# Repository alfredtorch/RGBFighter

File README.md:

🚥 Micro ESP-01 board for addressable pixel control 🚥 ... suits to every place and mostly to any needs!
Only a power bank and a smartphone are needed and you're good to go with your mobile setup.

* Small : +- 14x32mm & Lightweight : +- 4gr
* ESP8266 based (Support for Arduino)
* Designed for common LED Strips like WS2812 with level shifting
* Connection over 2,54 mm 3 Pin for direct soldering, JST or screw terminal (Version Strip or Panel)
* Power and Progamming over USB (CP2104 nodeMCU design)
* User Input for One Button OR IR Receiver
* [WLED](https://github.com/Aircoookie/WLED "WLED's Github page") compatible
* Inspirations from Adafruit, Sparkfun and many others

# ⚡️PCB 

# 🔦 Hardware

At the moment I have no possibility for a larger production and distribution. Of course, I am ready for any cooperation to industrialize the production. Happy to get any proposition.

## 🗺 Design Files

Designed in Eagle, in a messy way! Sorry! The related files are available under /Hardware.
Name | Description 
--- | ---
ButtonPanel | Panel and Button
ButtonStrip | Strip and Button
IR | Strip and IR Receiver
PowerRail | Power for 8 Strips
PowerDistributorX30 | 5 Ports XT-30 Connector

## 🛠 For DIY'er:
All you need are steady hands for the soldering part, specially the QFN. A reflow or hot plate is suggested.
The thickness of the board should be 1,2mm in order to sold the vertical USB firmly. The parts can be easily ordered from the common suppliers.

## 💰BOM

Part Name | Quantity | Price | Supply Link | Notes 
--- | --- | --- | --- | ---
Board RGBFighter | 1 | 0,02€ | [DirtyCheapPCB](https://dirtypcbs.com/store/pcbs/buy/108056/rgborder10x10january2019-zip) | Panelised Design files of Panel-Strip-USB Versions
ESP-01 MCU | 1x | 2€ | [Amazon](https://amzn.to/3qxXip7) | The brain with Wifi!
CP2104 USB Controller | 1x | 3€ | Mouser, ... | need for progamming : alternative [ESP-01 Flasher Amazon](https://amzn.to/3A2HptF) - [Aliexpress](https://s.click.aliexpress.com/e/_9JcISN)
Micro USB Vertical | 1x | 0,5€ | [Aliexpress](https://s.click.aliexpress.com/e/_AaeVzr)
Resistor Array 603 10k | 2x | 0,2€ | Mouser, ... | Pull-up registors for programming and normal operation
Transistor MMBT2222 | 2x | 0,2€ | Mouser, ... | need for programming, NPN Type
Capacitor 0805 | 3x | 0,2€ | Mouser, ... | Various values : schematics
Inducator 2.2uH | 1x | 0,2€ | Mouser, ... | NRH2412T2R2MNGH
3V3 Step Down Converter | 1x | 1,2€ | Mouser, ... | LM3671
Reistor 300Ohm 0805 | 1x | 0,2€ | Mouser, ... | basic pin protection 
Level Shifter SN74LVC1T45DBV  | 1x | 0,2€ | Mouser, ... | for the right Voltage on the Data bus
Button G71Y | 2x | 0,2€ | [Aliexpress](https://s.click.aliexpress.com/e/_A68Ds9) | MCU & Reset User Input
IR Receiver | 1x | 0,2€ | [Aliexpress](https://s.click.aliexpress.com/e/_A7jhiZ) |IR Control Version

🙏 Please if you need to shop for parts, it would be great that you use the supply links below. As they are affilated, you're supporting me directly to continue to deliver new projects to the community! Thank you ❤️

# 🎆 Versions

# 📖 History and Evaluation

It started longtime ago when I wanted an easy way to drive my pixels. First pcb version was sended to fabrication in july 2016. 
Since the project evolved into something more advanced and more mature!

## 🔍 Development Phase
ToDo | Remarks
--- | --- 
Easy Boards | Design boards without programming chip but with easy to solder buttons and voltage converter 
Documentation | Improve the transfer of knowledge
Big production | Looking forward to have some input, help to release it massivly, if wanted.

# 🛒 Accessories

Most of these parts can be laser cutted. The related files are available under Hardware/RGBFighterLaserParts.dxf

# 👶🏼 First Steps & Ideas

⚠️Don't mess with the power - no polarity or whatever protection ⚠️

⚠️Vertical USB is fragile - Handle with care ⚠️

## 🤏🏽 Pinout
Pin | Function
--- | ---
GPIO0 | Button Or InfraRed
GPIO2 | RGB Output | Recomanded Output from WLED

## 💾 Programming
You can directly check the [How-To from WLED](https://kno.wled.ge/basics/install-binary/)

## 🪛 Tutorials
see [Tutorials Page](https://github.com/alfredtorch/RGBFighter/blob/master/Tutorials.md)

Servo, Electro-Dipped, ...

---

# ⚖️ Licence
The MIT License (MIT)

Copyright (c) 2021 Max Schmit

Permission is hereby granted, free of charge, to any person obtaining a copy of this Hardware and associated documentation files (the "Hardware"), to deal in the Hardware without restriction, including without limitation the rights to use, copy, modify, merge, publish, distribute, sublicense, and/or sell copies of the Hardware, and to permit persons to whom the Hardware is furnished to do so, subject to the following conditions:

The above copyright notice and this permission notice shall be included in all copies or substantial portions of the Software.

THE HARDWARE IS PROVIDED "AS IS", WITHOUT WARRANTY OF ANY KIND, EXPRESS OR IMPLIED, INCLUDING BUT NOT LIMITED TO THE WARRANTIES OF MERCHANTABILITY, FITNESS FOR A PARTICULAR PURPOSE AND NONINFRINGEMENT. IN NO EVENT SHALL THE AUTHORS OR COPYRIGHT HOLDERS BE LIABLE FOR ANY CLAIM, DAMAGES OR OTHER LIABILITY, WHETHER IN AN ACTION OF CONTRACT, TORT OR OTHERWISE, ARISING FROM, OUT OF OR IN CONNECTION WITH THE SOFTWARE OR THE USE OR OTHER DEALINGS IN THE SOFTWARE.

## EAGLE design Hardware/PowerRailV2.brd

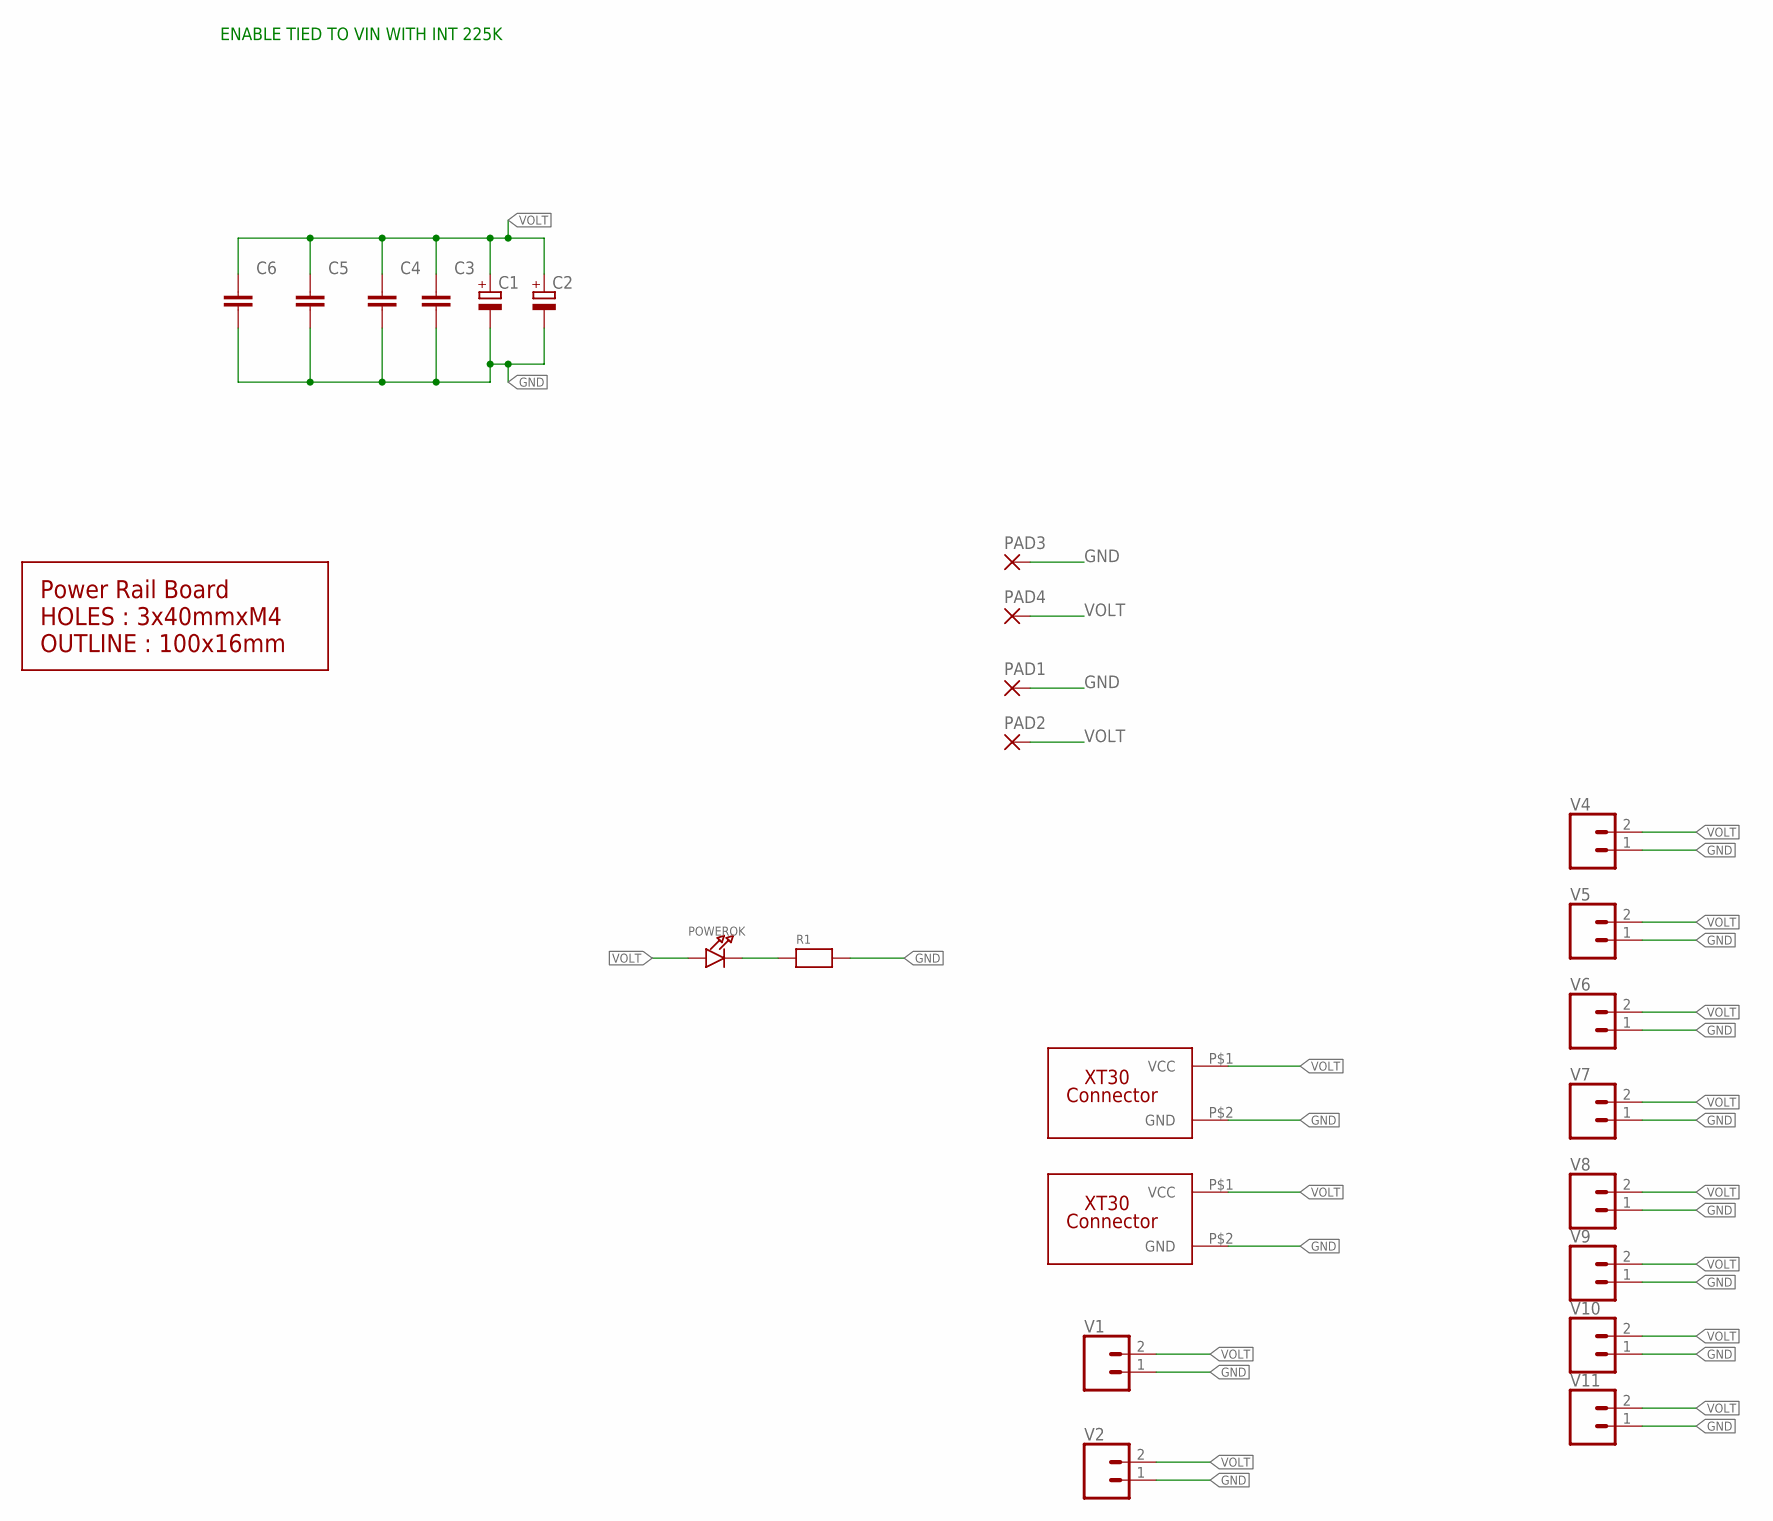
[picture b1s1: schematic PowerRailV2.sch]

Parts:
C1, C2: CPOL-EUE5-6; E5-6
C3, C4: CAPACITOR_NPOL-0805; C805
C5, C6: CAPACITOR_NPOL-1206; C1206
PAD1, PAD2, PAD3, PAD4: SMD2; SMD1,27-2,54
POWEROK: LED0805; CHIPLED_0805
R1: RESISTOR0805; 0805
U$3: BOARD_POWERRAI_PCB; POWERRAIL_8-LED
U$4, U$6: XT30; XT30-VERT
V1, V2, V4, V5, V6, V7, V8, V9, V10, V11: CONN_023.5MM; SCREWTERMINAL-3.5MM-2

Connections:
GND: C1.-, C2.-, C3.2, C4.2, C5.2, C6.2, PAD1.1, PAD3.1, R1.2, U$4.P$2 (GND), U$6.P$2 (GND), V1.1, V2.1, V4.1, V5.1, V6.1, V7.1, V8.1, V9.1, V10.1, V11.1
unnamed: POWEROK.C, R1.1
VOLT: C1.+, C2.+, C3.1, C4.1, C5.1, C6.1, PAD2.1, PAD4.1, POWEROK.A, U$4.P$1 (VCC), U$6.P$1 (VCC), V1.2, V2.2, V4.2, V5.2, V6.2, V7.2, V8.2, V9.2, V10.2, V11.2

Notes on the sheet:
ENABLE TIED TO VIN WITH INT 225K

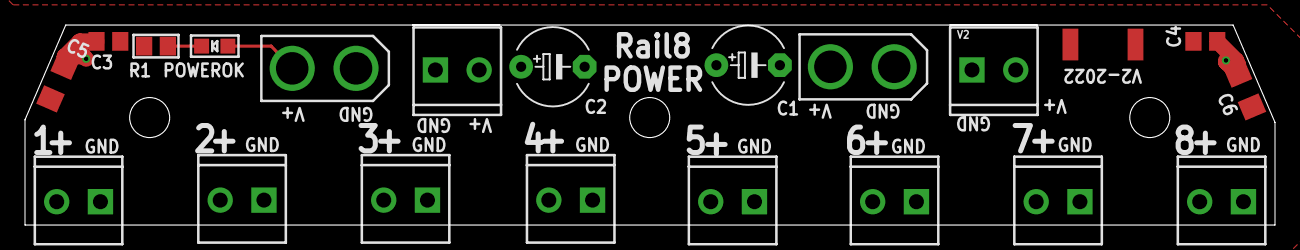
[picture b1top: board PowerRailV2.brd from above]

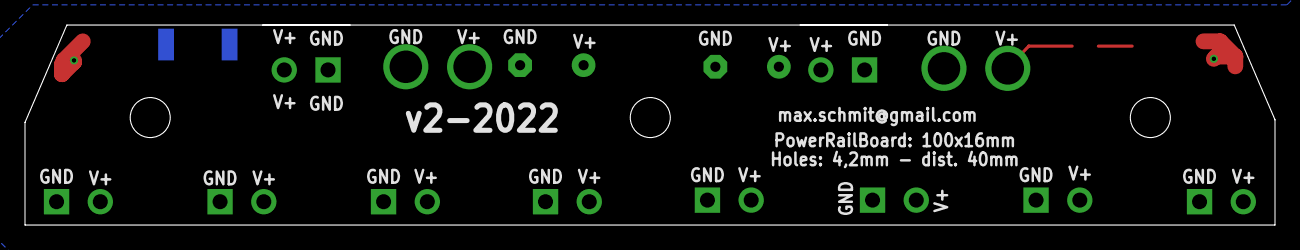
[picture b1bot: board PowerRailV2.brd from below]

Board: 2 copper layers, 100.0 x 16.0 mm, 25 parts (2 on the bottom side), 3 nets.

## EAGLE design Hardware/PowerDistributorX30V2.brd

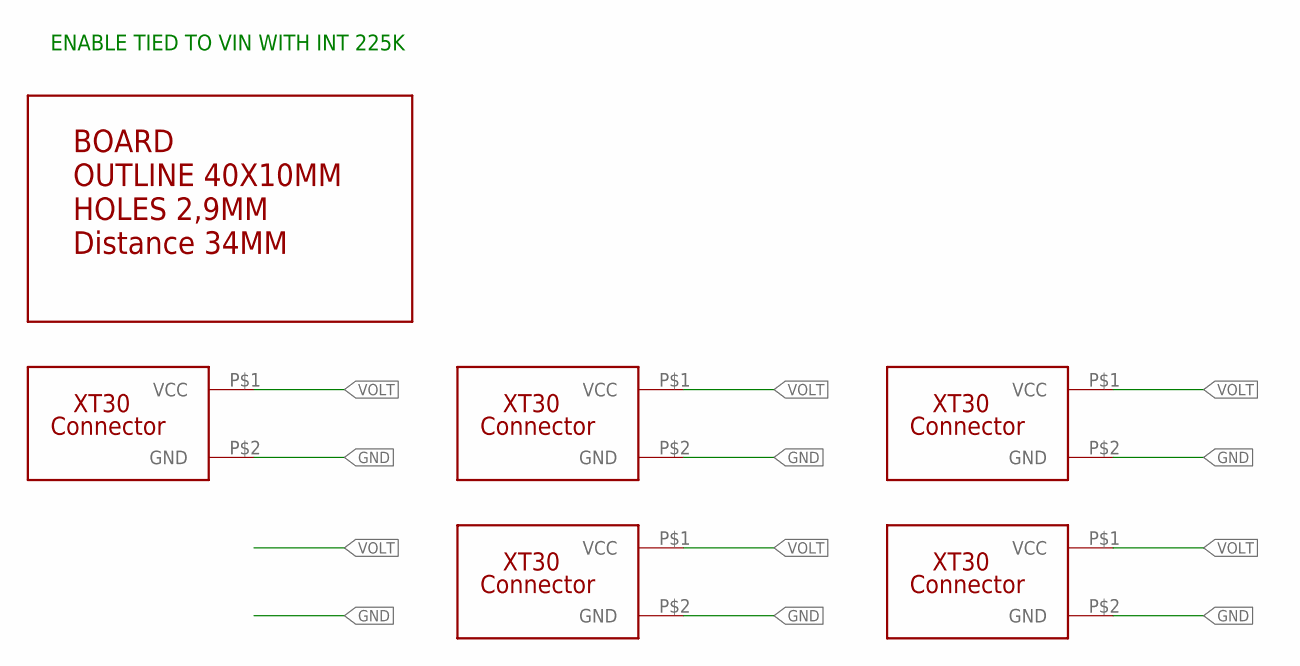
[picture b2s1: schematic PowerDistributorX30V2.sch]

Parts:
U$1: BOARD40X10; BOARD_40X10-34HOLES
U$2, U$4, U$5, U$6, U$7: XT30; XT30-VERT

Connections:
GND: U$2.P$2 (GND), U$4.P$2 (GND), U$5.P$2 (GND), U$6.P$2 (GND), U$7.P$2 (GND)
VOLT: U$2.P$1 (VCC), U$4.P$1 (VCC), U$5.P$1 (VCC), U$6.P$1 (VCC), U$7.P$1 (VCC)

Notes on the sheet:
ENABLE TIED TO VIN WITH INT 225K

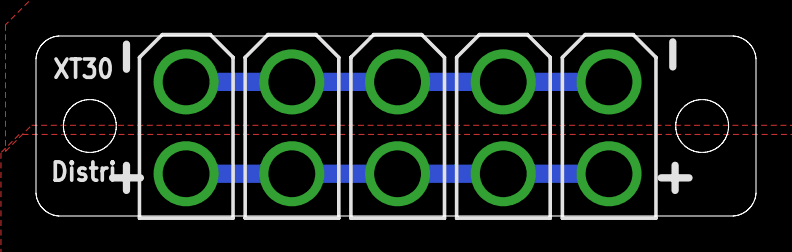
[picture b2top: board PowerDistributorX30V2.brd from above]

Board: 2 copper layers, 40.0 x 10.0 mm, 6 parts (0 on the bottom side), 2 nets.

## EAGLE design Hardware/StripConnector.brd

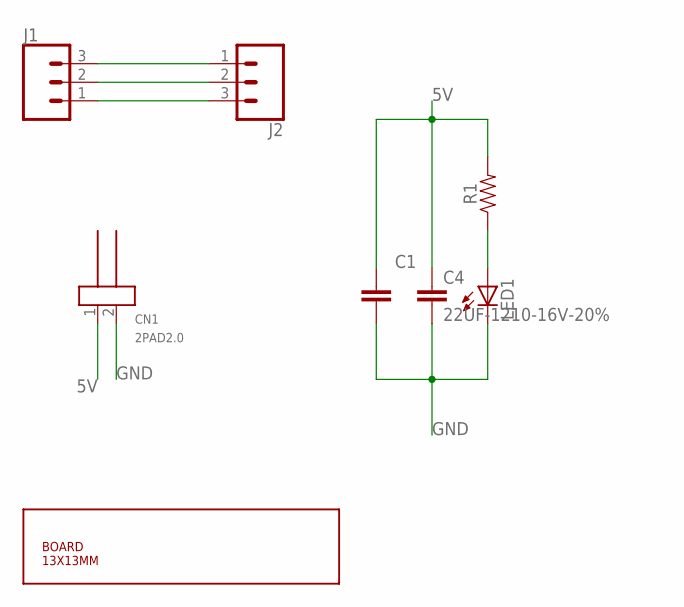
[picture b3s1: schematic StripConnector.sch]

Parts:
C1: CAPACITOR_NPOL-0805; C805
C4: 22UF-1210-16V-20%; 1210
CN1: 2PAD2.0; 2POLE_P2.0
J1, J2: CONN_03LONGPADS; 1X03_LONGPADS
LED1: LED-0805; LED-805
R1: 0805
U$1: BOARD_13X13MM; 13X13

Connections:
5V: C1.1, C4.1, CN1.1, J1.1, J2.3, R1.2
DATA: J1.2, J2.2
GND: C1.2, C4.2, CN1.2, J1.3, J2.1, LED1.C
unnamed: LED1.A, R1.1

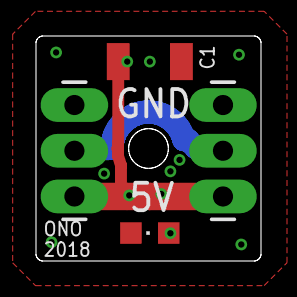
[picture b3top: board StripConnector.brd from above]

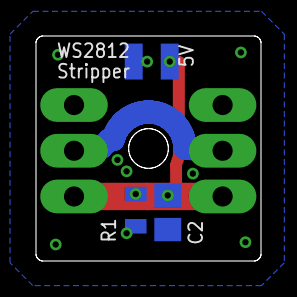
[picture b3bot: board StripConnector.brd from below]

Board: 2 copper layers, 12.5 x 12.5 mm, 8 parts (3 on the bottom side), 4 nets.

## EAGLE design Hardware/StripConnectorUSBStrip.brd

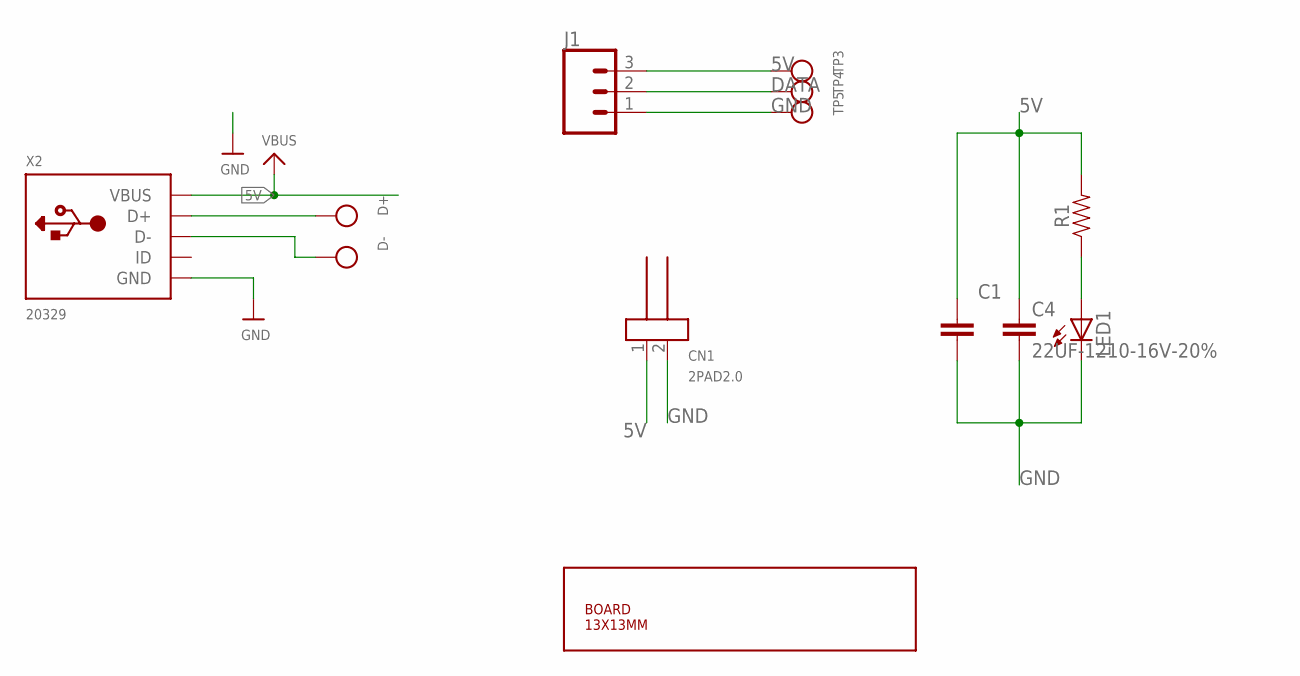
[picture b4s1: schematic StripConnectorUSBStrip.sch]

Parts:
C1: CAPACITOR_NPOL-0805; C805
C4: 22UF-1210-16V-20%; 1210
CN1: 2PAD2.0; 2POLE_P2.0
D+: TESTPOINTROUND1MM; TESTPOINT_ROUND_1MM
D-: TESTPOINTROUND1MM; TESTPOINT_ROUND_1MM
J1: CONN_03LONGPADS; 1X03_LONGPADS
LED1: LED-0805; LED-805
R1: 0805
TP3, TP4, TP5: TESTPOINTROUND1MM; TESTPOINT_ROUND_1MM
U$1: BOARD_13X13MM; 13X13
X2: 20329; 4UCONN_20329_V2

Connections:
5V: C1.1, C4.1, CN1.1, J1.3, R1.2, TP3.P$1, X2.VBUS
DATA: J1.2, TP4.P$1
GND: C1.2, C4.2, CN1.2, J1.1, LED1.C, TP5.P$1, X2.BASE@1 (GND), X2.BASE@2 (GND), X2.GND, X2.SPRT@1 (GND), X2.SPRT@2 (GND), X2.SPRT@3 (GND), X2.SPRT@4 (GND)
unnamed: D-.P$1, X2.D-
unnamed: LED1.A, R1.1
unnamed: D+.P$1, X2.D+

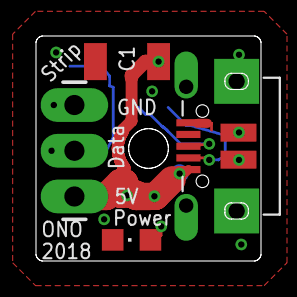
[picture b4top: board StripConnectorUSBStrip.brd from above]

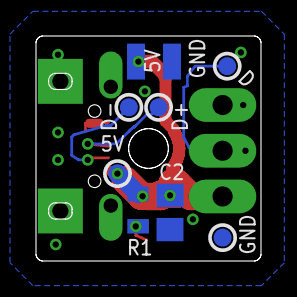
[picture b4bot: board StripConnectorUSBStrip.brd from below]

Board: 2 copper layers, 12.5 x 12.5 mm, 13 parts (8 on the bottom side), 6 nets.

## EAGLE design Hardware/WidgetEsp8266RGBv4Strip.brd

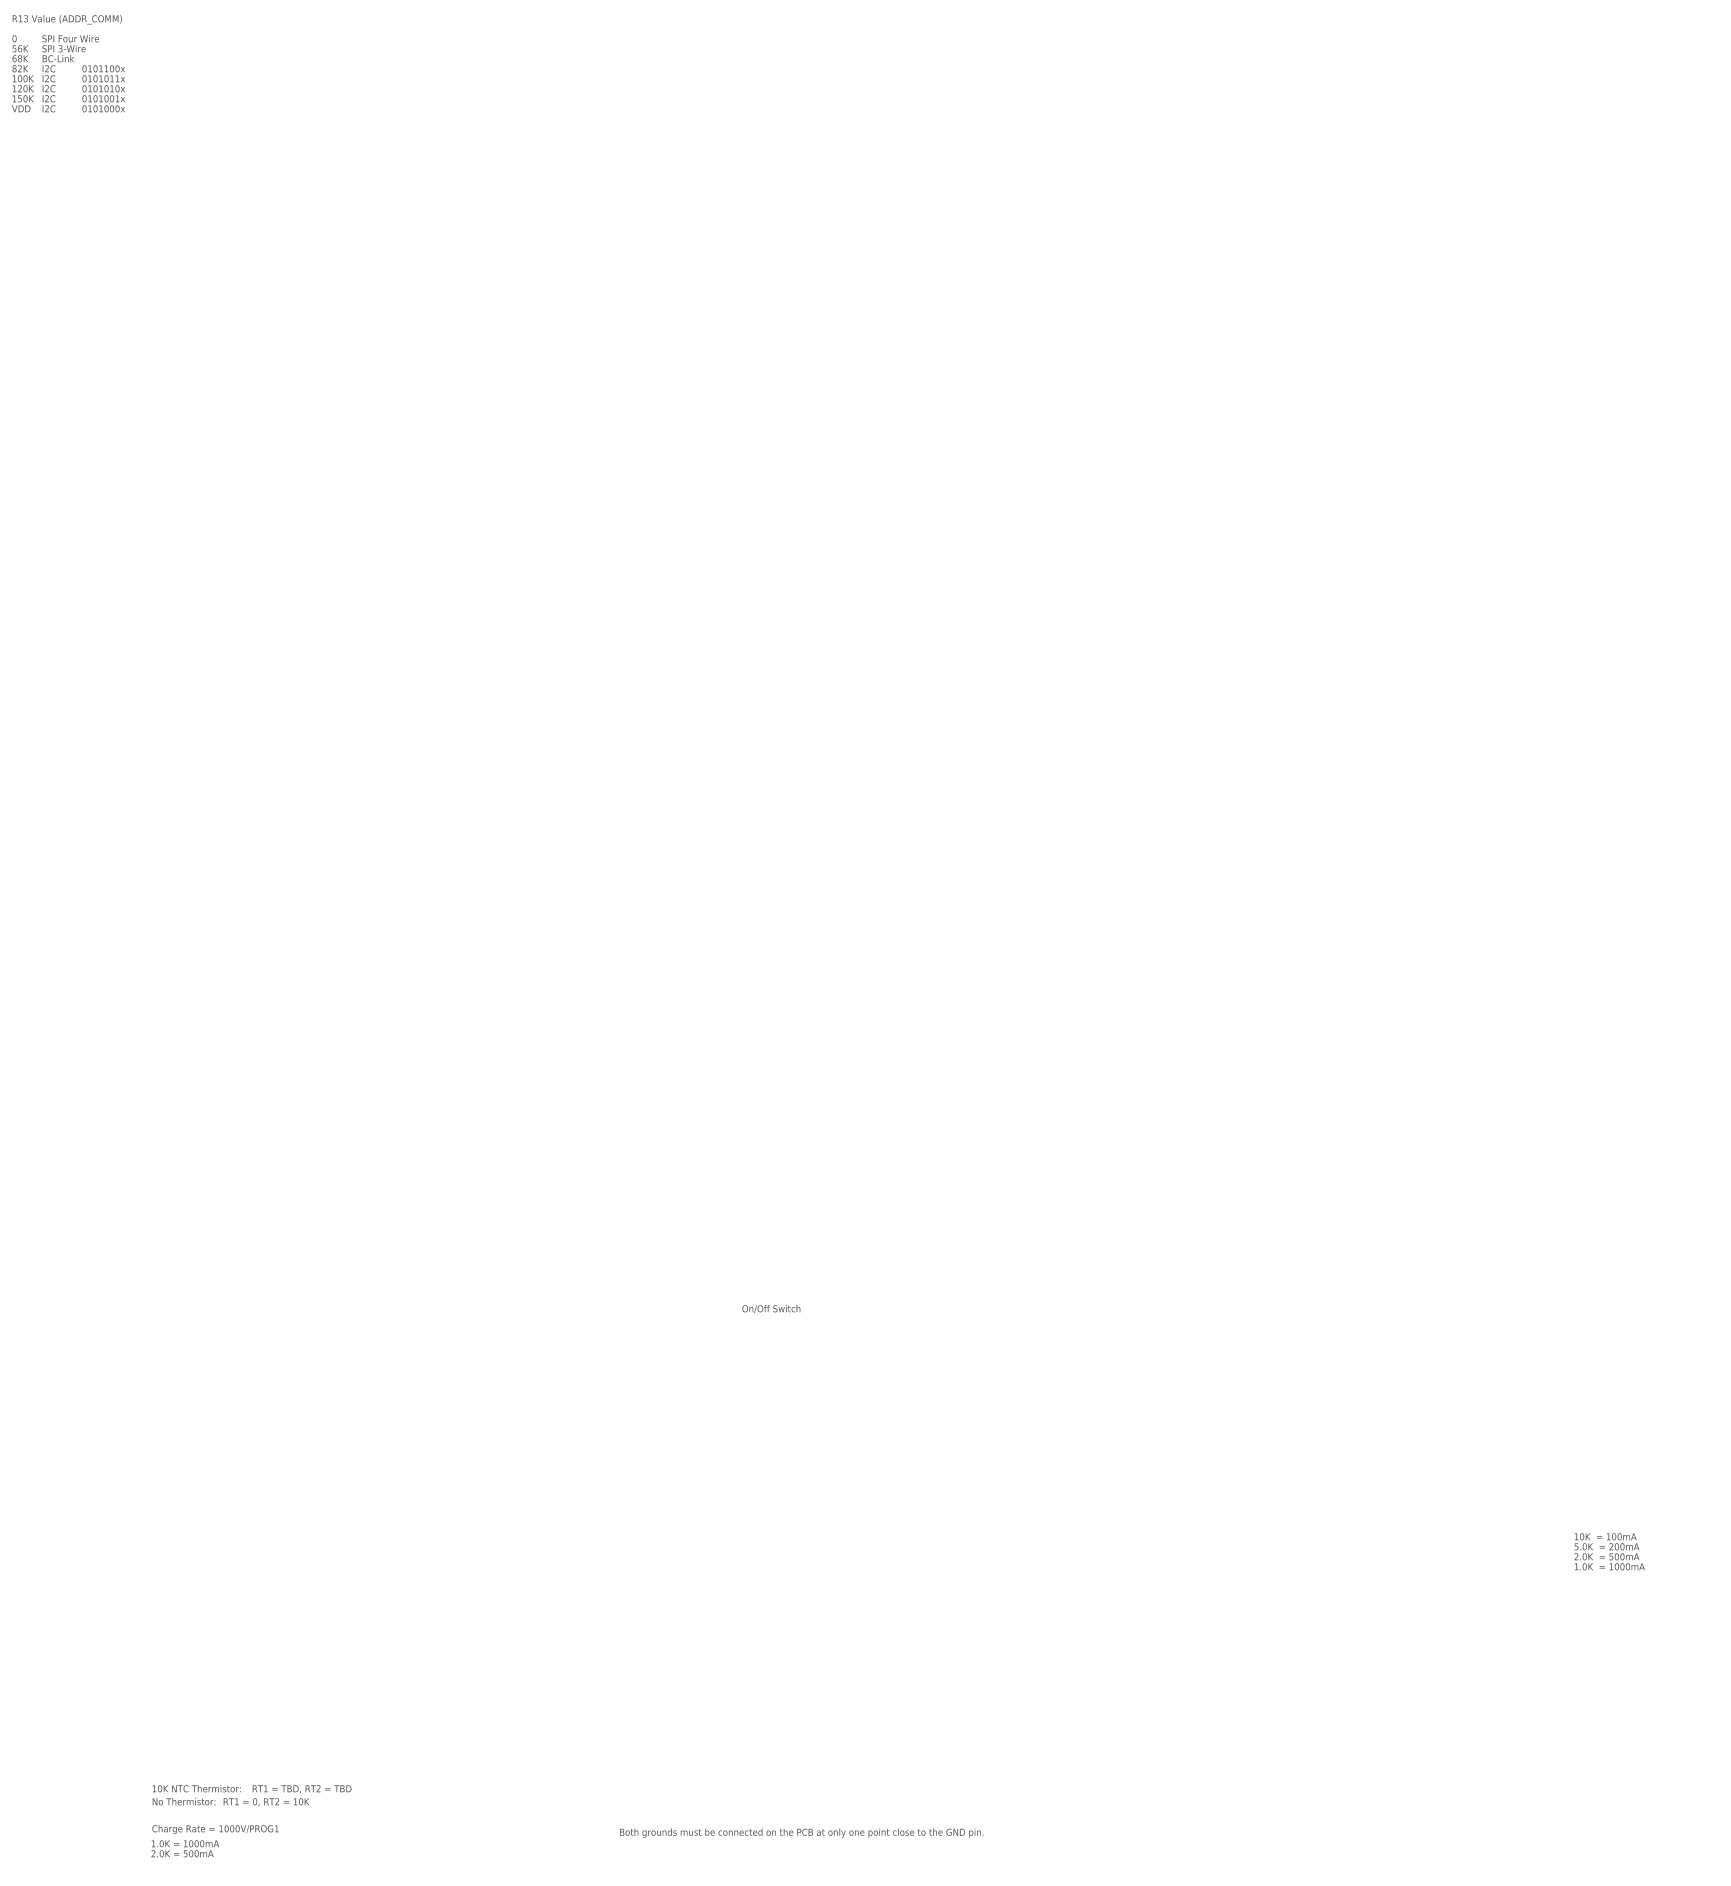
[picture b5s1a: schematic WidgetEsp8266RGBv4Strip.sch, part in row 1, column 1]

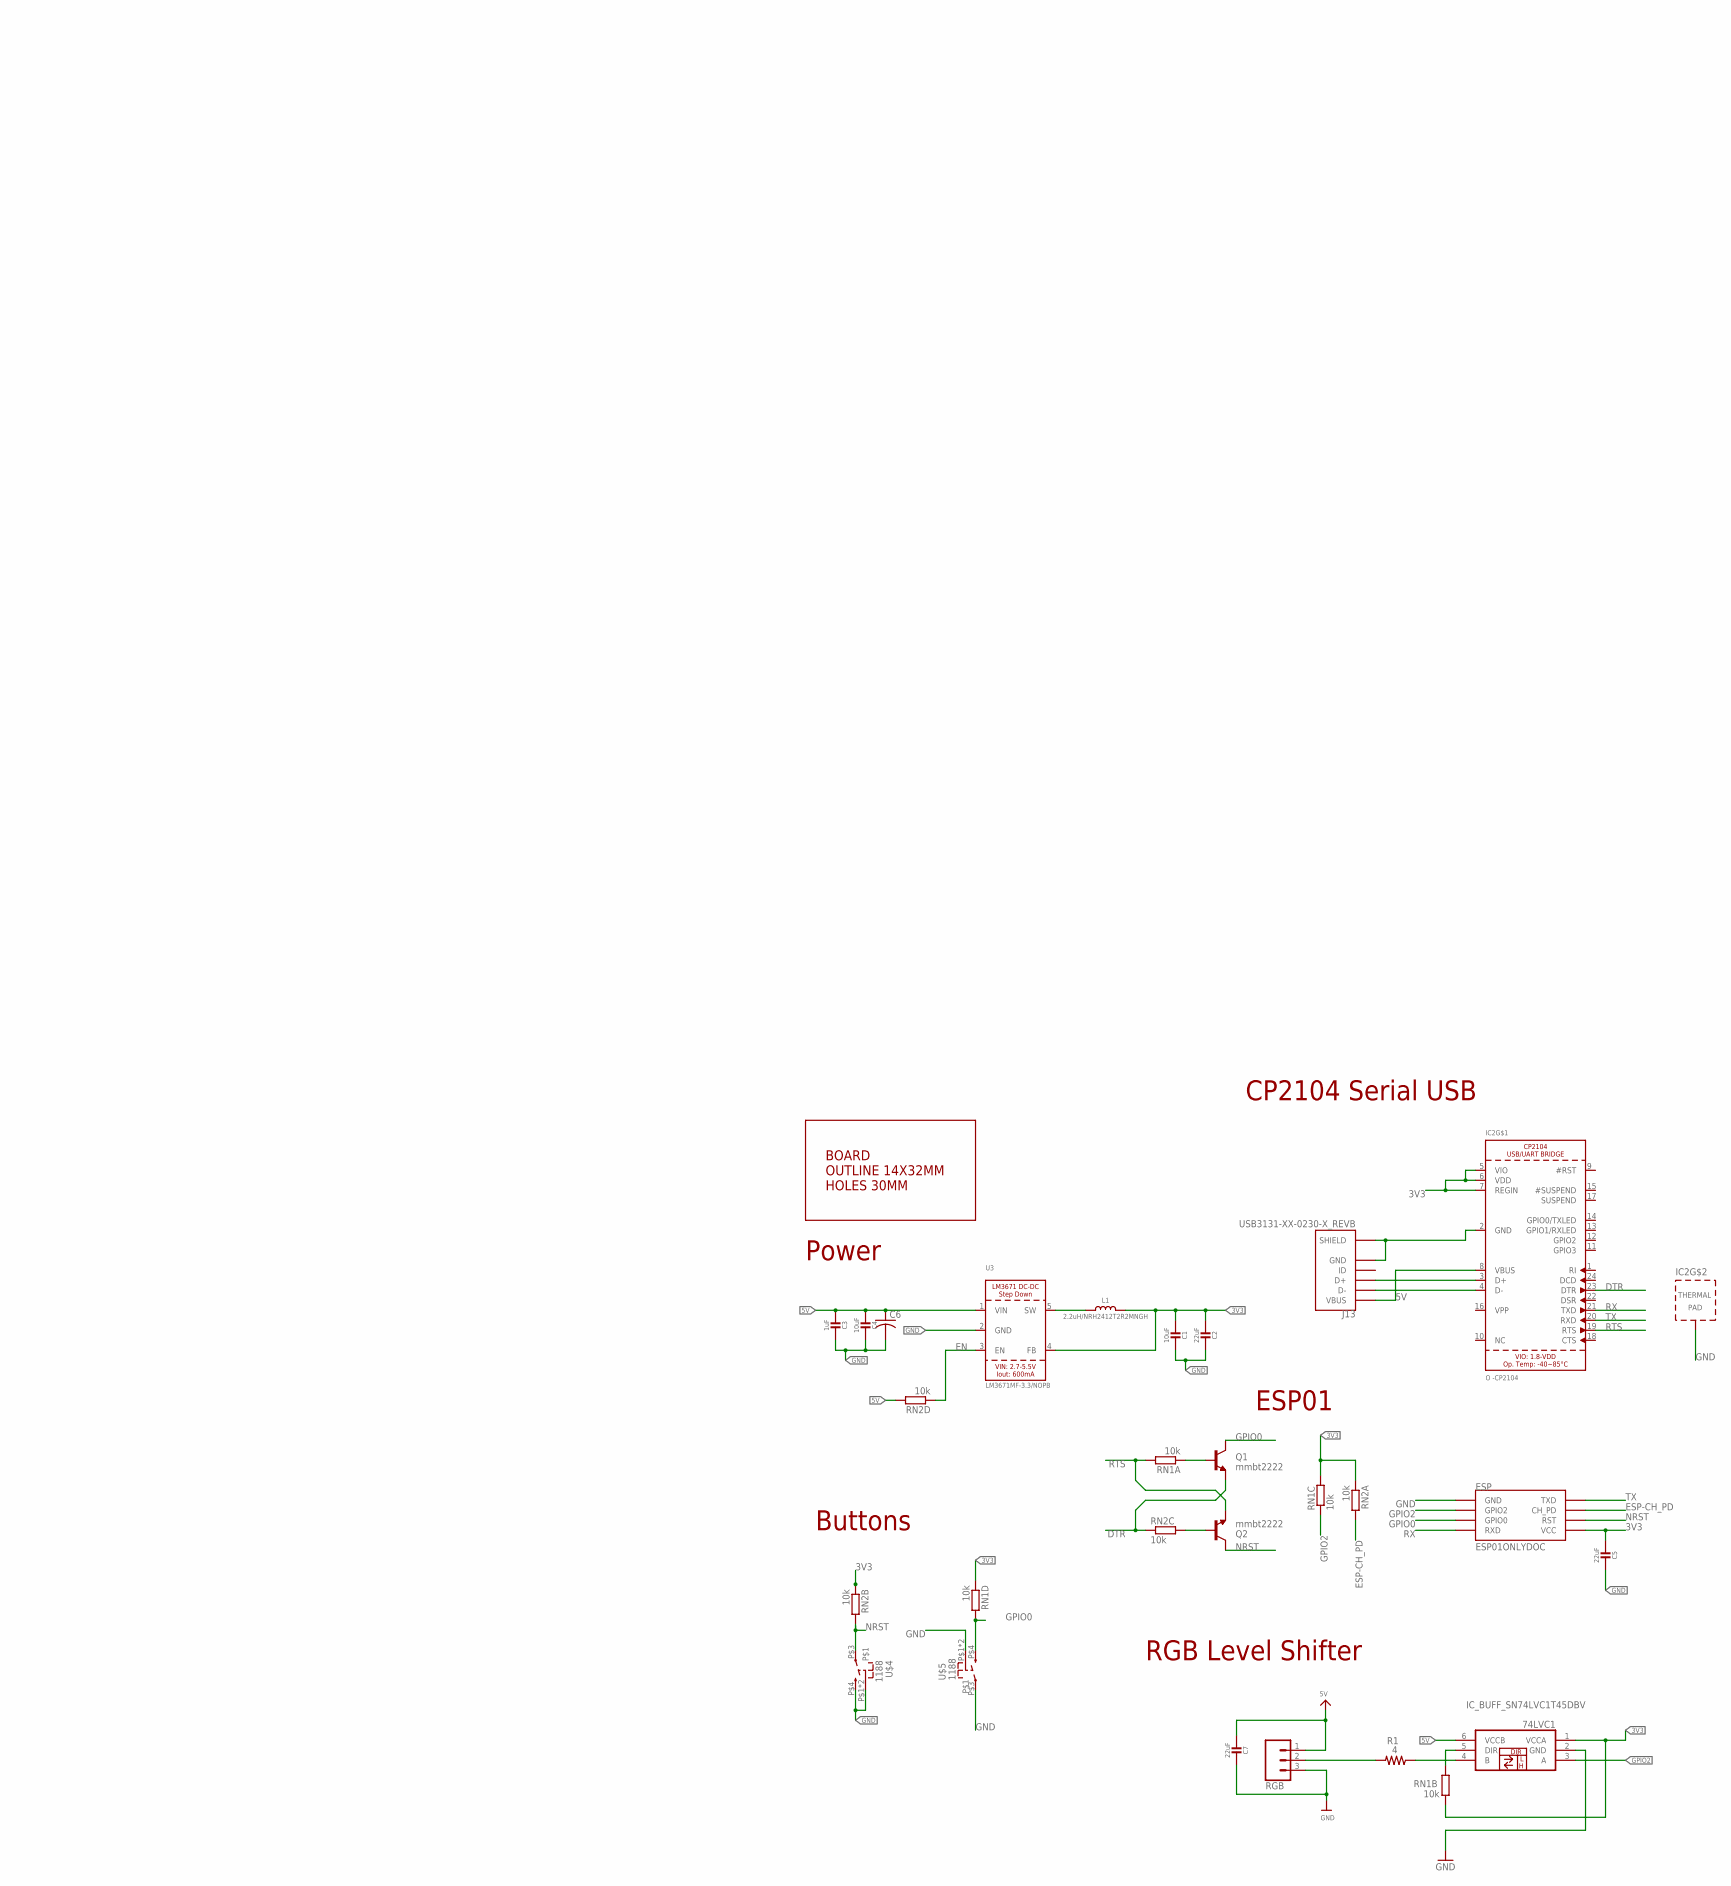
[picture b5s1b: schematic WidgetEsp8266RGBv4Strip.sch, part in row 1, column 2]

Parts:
74LVC1: IC_BUFF_SN74LVC1T45DBV; DBV-R-PDSO-G6
C1, C4: 10uF; 0805-NO
C2, C5, C7: 22uF; 0805-NO
C3: 1uF; 0805-NO
C6: C-USC3225; C3225
ESP: ESP01ONLYDOC; ESP01-NONOSILK
IC2: O -CP2104; QFN24_4MM_SMSC
J13: USB3131-XX-0230-X_REVB; GCT_USB3131-XX-0230-X_REVB
L1: 2.2uH/NRH2412T2R2MNGH; INDUCTOR_TAIYOYUDEN_NRH2412T
Q1, Q2: mmbt2222; SOT23-3
R1: 4; 0805
RGB: CONN_03LONGPADS; 1X03_LONGPADS
RN1, RN2: 10k; RN8P-4R-CRA06S
U3: LM3671MF-3.3/NOPB; SOT23-5
U$4, U$5: 1188
U$7: BOARD14X32; 14X32

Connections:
3V3: 74LVC1.1 (VCCA), C1.2, C2.2, C5.2, ESP.VCC, IC2.5 (VIO), IC2.6 (VDD), IC2.7 (REGIN), L1.2, RN1.4 (1), RN1.6 (2), RN1.7 (2), RN2.1, RN2.2 (1), U3.4 (FB)
5V: 74LVC1.6 (VCCB), C3.2, C4.2, C6.1, C7.2, IC2.8 (VBUS), J13.1 (VBUS), RGB.1, RN2.5 (2), U3.1 (VIN)
DTR: IC2.23 (DTR), Q1.2 (E), RN2.3 (1)
EN: RN2.4 (1), U3.3 (EN)
ESP-CH_PD: ESP.CH_PD, RN2.8 (2)
ESP-USBMINUS3: IC2.4 (D-), J13.2 (D-)
ESP-USBPLUS3: IC2.3 (D+), J13.3 (D+)
GND: 74LVC1.2 (GND), C1.1, C2.1, C3.1, C4.1, C5.1, C6.2, C7.1, ESP.GND, IC2.2 (GND), IC2.THERM (TP), J13.5 (GND), J13.6 (SHIELD), J13.7 (SHIELD), RGB.3, U3.2 (GND), U$4.P$1, U$4.P$2, U$4.P$4 (3), U$5.P$1, U$5.P$2, U$5.P$3 (1)
GPIO0: ESP.GPIO0, Q1.3 (C), RN1.5 (2), U$5.P$4 (3)
GPIO2: 74LVC1.3 (A), ESP.GPIO2, RN1.3 (1)
unnamed: Q2.1 (B), RN2.6 (2)
unnamed: L1.1, U3.5 (SW)
unnamed: Q1.1 (B), RN1.1
unnamed: 74LVC1.5 (DIR), RN1.2 (1)
unnamed: 74LVC1.4 (B), R1.1
NRST: ESP.RST, Q2.3 (C), RN2.7 (2), U$4.P$3 (1)
RTS: IC2.19 (RTS), Q2.2 (E), RN1.8 (2)
RX: ESP.RX (RXD), IC2.21 (TXD)
TO-RGB-TOP: R1.2, RGB.2
TX: ESP.TX (TXD), IC2.20 (RXD)

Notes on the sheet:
R13 Value (ADDR_COMM)
SPI Four Wire
56K
SPI 3-Wire
68K
BC-Link
82K
I2C
0101100x
0101011x
0101010x
0101001x
0101000x
100K
120K
150K
VDD
Both grounds must be connected on the PCB at only one point close to the GND pin.
On/Off Switch
Charge Rate = 1000V/PROG1
1.0K = 1000mA
2.0K = 500mA
No Thermistor:
10K NTC Thermistor:
RT1 = 0, RT2 = 10K
RT1 = TBD, RT2 = TBD
10K = 100mA
5.0K = 200mA
2.0K = 500mA
1.0K = 1000mA
RGB Level Shifter
Buttons
CP2104 Serial USB
ESP01
Power

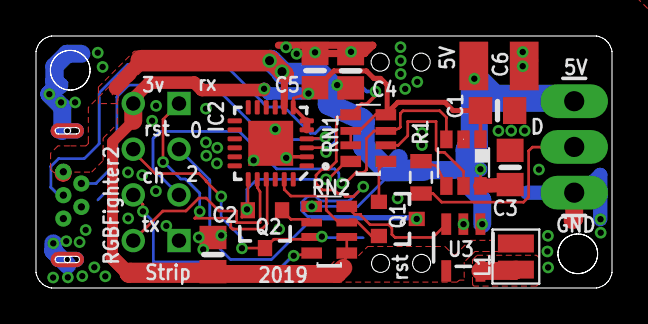
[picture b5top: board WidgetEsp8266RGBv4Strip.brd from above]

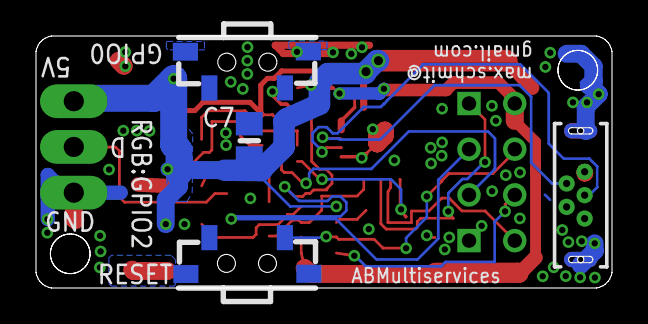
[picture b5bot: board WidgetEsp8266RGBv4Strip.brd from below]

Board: 2 copper layers, 32.0 x 14.0 mm, 22 parts (6 on the bottom side), 20 nets.

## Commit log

2022-01-12 Create test
2022-01-13 added
2022-01-13 Create Hardware
2024-05-07 Create StageFighter
2024-05-07 Rename StageFighter to StageFighter.md

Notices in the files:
parts and their libraries:
SparkFun-Connectors: Licensing: Creative Commons ShareAlike 4.0 International - https://creativecommons.org/licenses/by-sa/4.0
microbuilder: This work is placed in the public domain, and may be freely used for commercial and non-commercial work with the following conditions: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
